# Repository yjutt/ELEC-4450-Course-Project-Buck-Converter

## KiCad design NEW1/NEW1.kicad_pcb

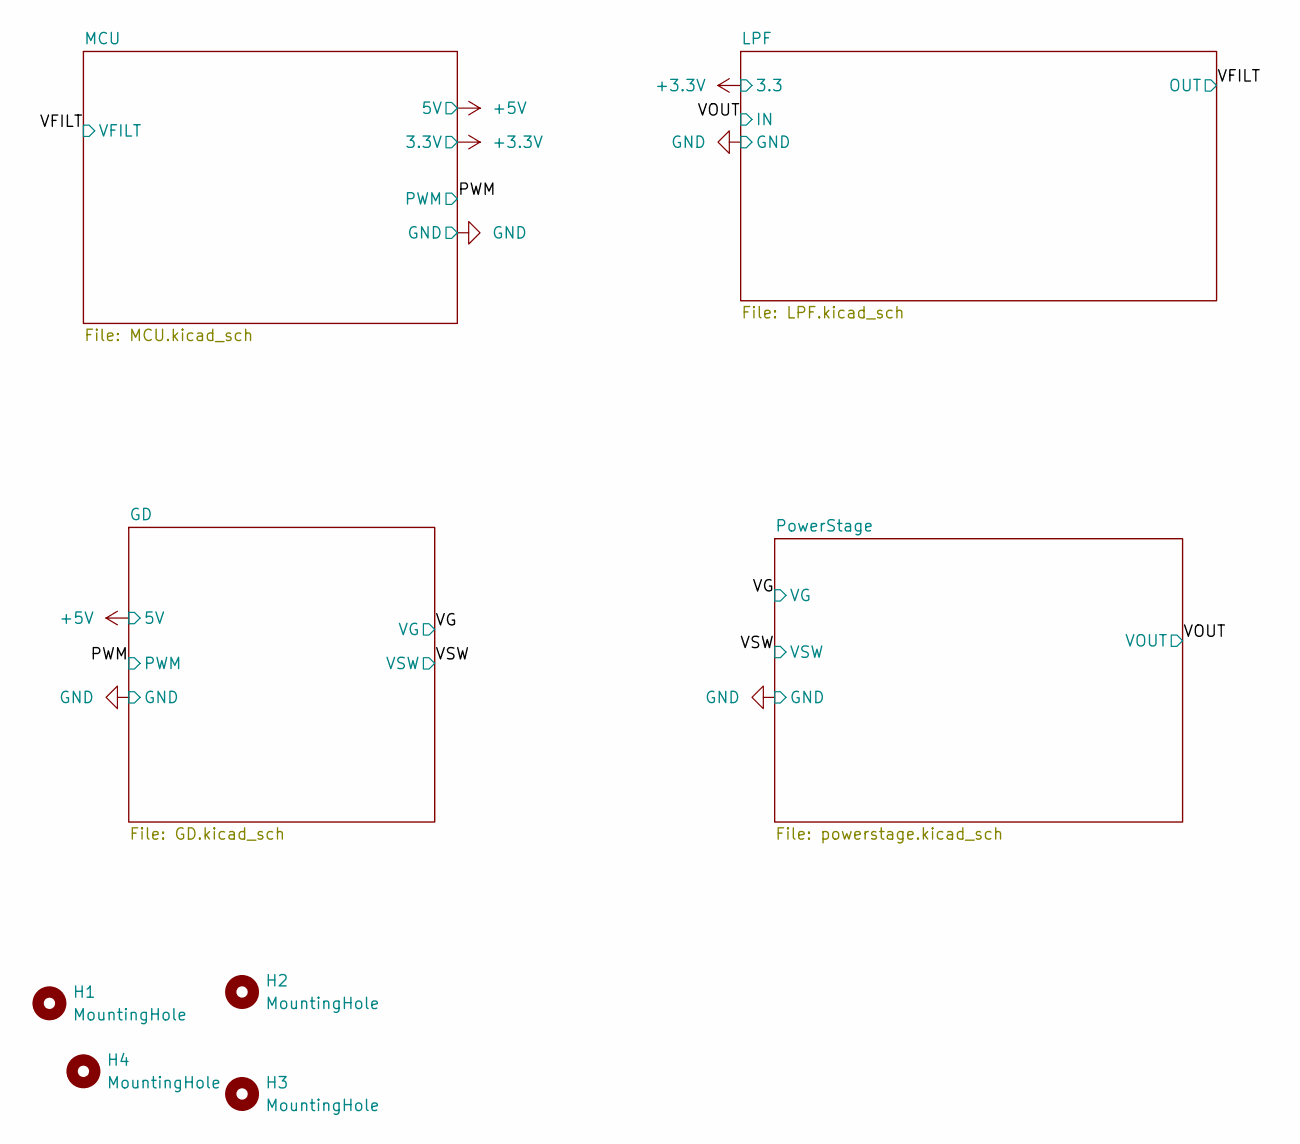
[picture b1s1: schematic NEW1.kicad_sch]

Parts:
H1, H2, H3, H4: MountingHole; MountingHole_4mm; Part Number 971100244

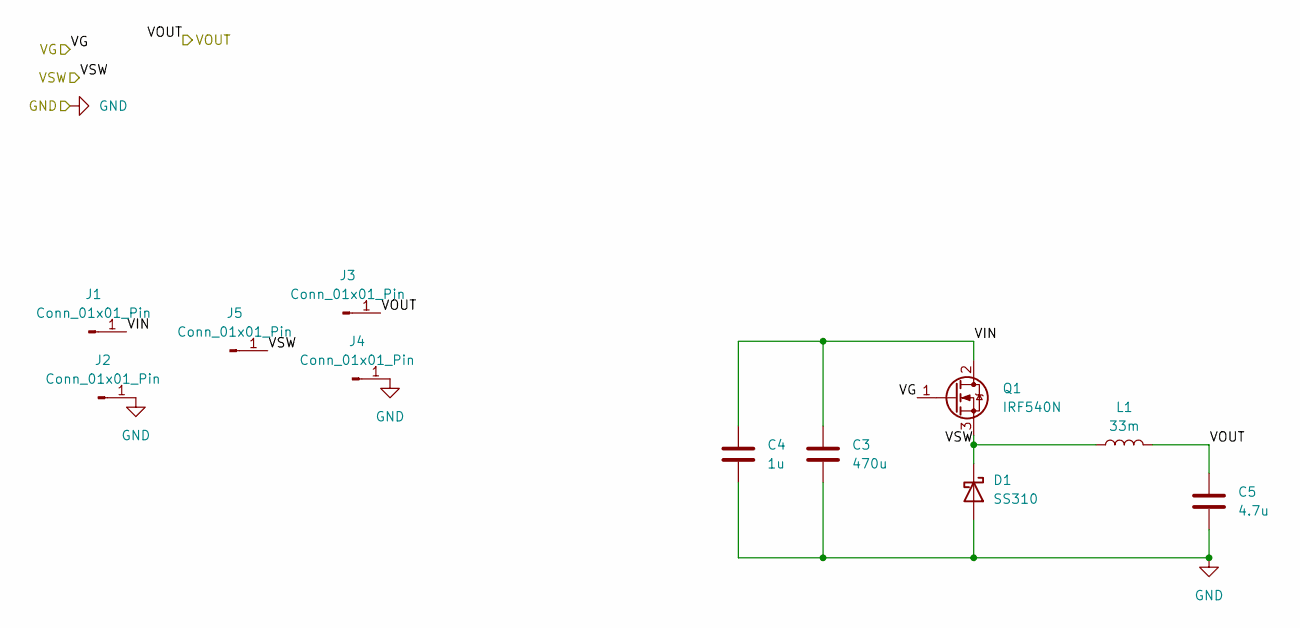
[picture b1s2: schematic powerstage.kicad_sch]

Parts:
C3: 470u; CP_Radial_D18.0mm_P7.50mm; Part Number 100ZLH470MEFC16X31.5
C4: 1u; C_0805_2012Metric; Part Number GRM21BC72A105KE01L
C5: 4.7u; C_1206_3216Metric; Part Number GRM31CC72A475KE11L
D1: SS310; D_SMA; Part Number SS310
J1, J2, J3, J4, J5: Conn_01x01_Pin; Banana_Jack_1Pin; Part Number BU-P72930-2
L1: 33m; L_Axial_L23.4mm_D12.7mm_P32.00mm_Horizontal_Vishay_IHA-203; Part Number 5900-333-RC
Q1: IRF540N; TO-220-3_Vertical; Part Number IRF540N

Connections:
/PowerStage/VIN: C3.1, C4.1, J1.1, Q1.2 (D)
/VG: Q1.1 (G); also elsewhere on the board
/VOUT: C5.1, J3.1, L1.2; also elsewhere on the board
/VSW: D1.1 (K), J5.1, L1.1, Q1.3 (S); also elsewhere on the board
GND: C3.2, C4.2, C5.2, D1.2 (A), J2.1, J4.1; also elsewhere on the board

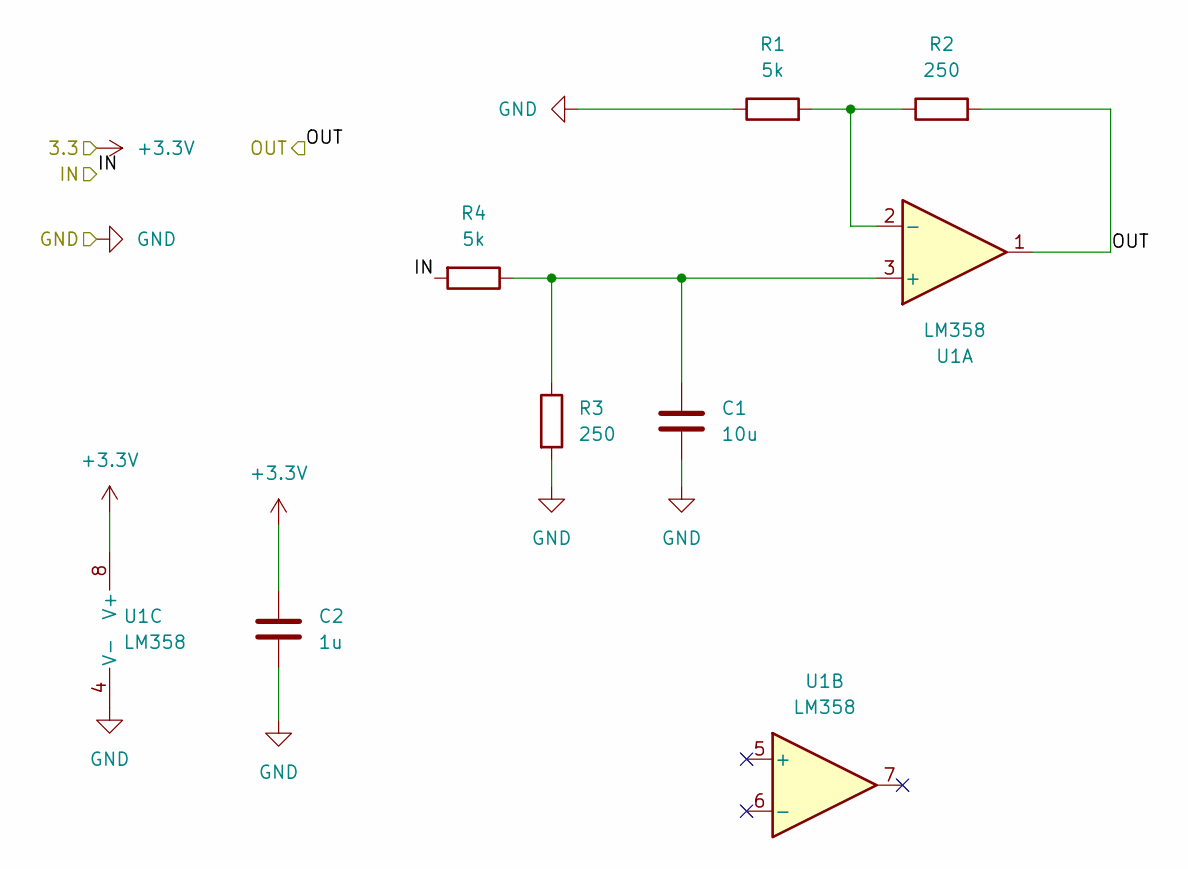
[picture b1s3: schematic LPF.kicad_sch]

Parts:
C1: 10u; C_0805_2012Metric; Part Number GRM21BR61C106KE15K
C2: 1u; C_0805_2012Metric; Part Number C0805C105K3RACTU
R1, R4: 5k; R_0805_2012Metric; Part Number CRT0805-BY-5001EAS
R2, R3: 250; R_0805_2012Metric; Part Number APC0805B250RN
U1: LM358; DIP-8_W7.62mm; Part Number LM358AP

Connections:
+3.3V: C2.1, U1.8 (V+); also elsewhere on the board
/VFILT: R2.2, U1.1; also elsewhere on the board
/VOUT: R4.2; also elsewhere on the board
GND: C1.2, C2.2, R1.1, R3.2, U1.4 (V-); also elsewhere on the board
unnamed: C1.1, R3.1, R4.1, U1.3 (+)
unnamed: R1.2, R2.1, U1.2 (-)

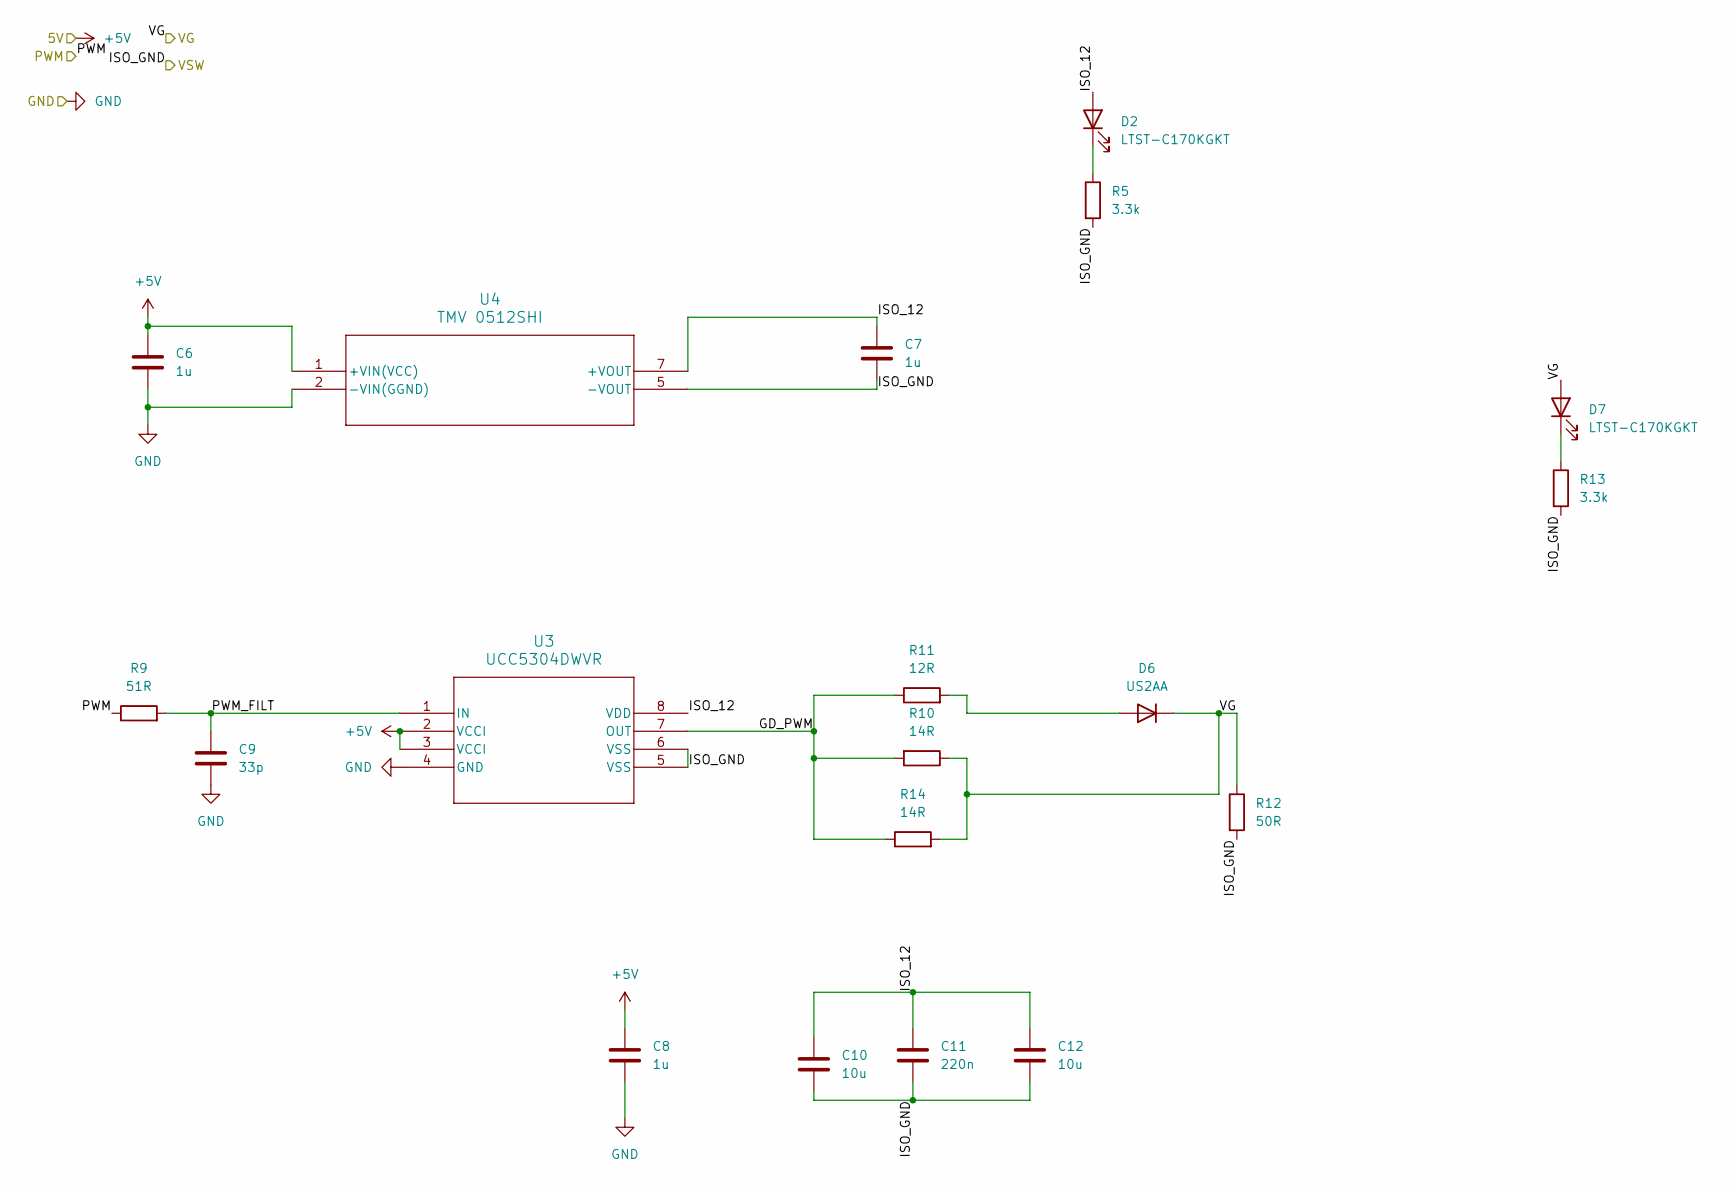
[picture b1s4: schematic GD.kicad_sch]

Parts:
C6, C7: 1u; C_0805_2012Metric; Part Number C0805C105K3RACTU
C8: 1u; C_0805_2012Metric_Pad1.18x1.45mm_HandSolder; Part Number C0805C105K3RACTU
C9: 33p; C_0805_2012Metric_Pad1.18x1.45mm_HandSolder; Part Number 600F330FT250XT4K
C10, C12: 10u; C_0805_2012Metric; Part Number F951C106MPAAQ2
C11: 220n; C_0805_2012Metric; Part Number C0805C224K5RACTU
D2, D7: LTST-C170KGKT; LED_0805_2012Metric; Part Number LTST-C170KGKT
D6: US2AA; D_SMA; Part Number US2AA
R5, R13: 3.3k; R_0805_2012Metric_Pad1.20x1.40mm_HandSolder; Part Number ERJ-P06F3301V
R9: 51R; R_0805_2012Metric_Pad1.20x1.40mm_HandSolder; Part Number RC0805FR-0751RL
R10, R14: 14R; R_0805_2012Metric_Pad1.20x1.40mm_HandSolder; Part Number RC0805FR-0714RL
R11: 12R; R_0805_2012Metric_Pad1.20x1.40mm_HandSolder; Part Number RC0805FR-0712RL
R12: 50R; R_1206_3216Metric_Pad1.30x1.75mm_HandSolder; Part Number RCP1206W50R0JTP
U3: UCC5304DWVR; SOIC8_DWV_TEX; Part Number UCC5304DWVR
U4: TMV 0512SHI; TMV-HI_SINGLE_TRP; Part Number TMV 0512SHI

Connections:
+5V: C6.1, C8.1, U3.2 (VCCI), U3.3 (VCCI), U4.1 (+VIN(VCC)); also elsewhere on the board
/GD/GD_PWM: R10.2, R11.1, R14.1, U3.7 (OUT)
/GD/ISO_12: C7.1, C10.1, C11.1, C12.1, D2.2 (A), U3.8 (VDD), U4.7 (+VOUT)
/GD/PWM_FILT: C9.1, R9.2, U3.1 (IN)
/PWM: R9.1; also elsewhere on the board
/VG: D6.1 (K), D7.2 (A), R10.1, R12.1, R14.2; also elsewhere on the board
/VSW: C7.2, C10.2, C11.2, C12.2, R5.2, R12.2, R13.2, U3.5 (VSS), U3.6 (VSS), U4.5 (-VOUT); also elsewhere on the board
GND: C6.2, C8.2, C9.2, U3.4 (GND), U4.2 (-VIN(GGND)); also elsewhere on the board
unnamed: D2.1 (K), R5.1
unnamed: D6.2 (A), R11.2
unnamed: D7.1 (K), R13.1

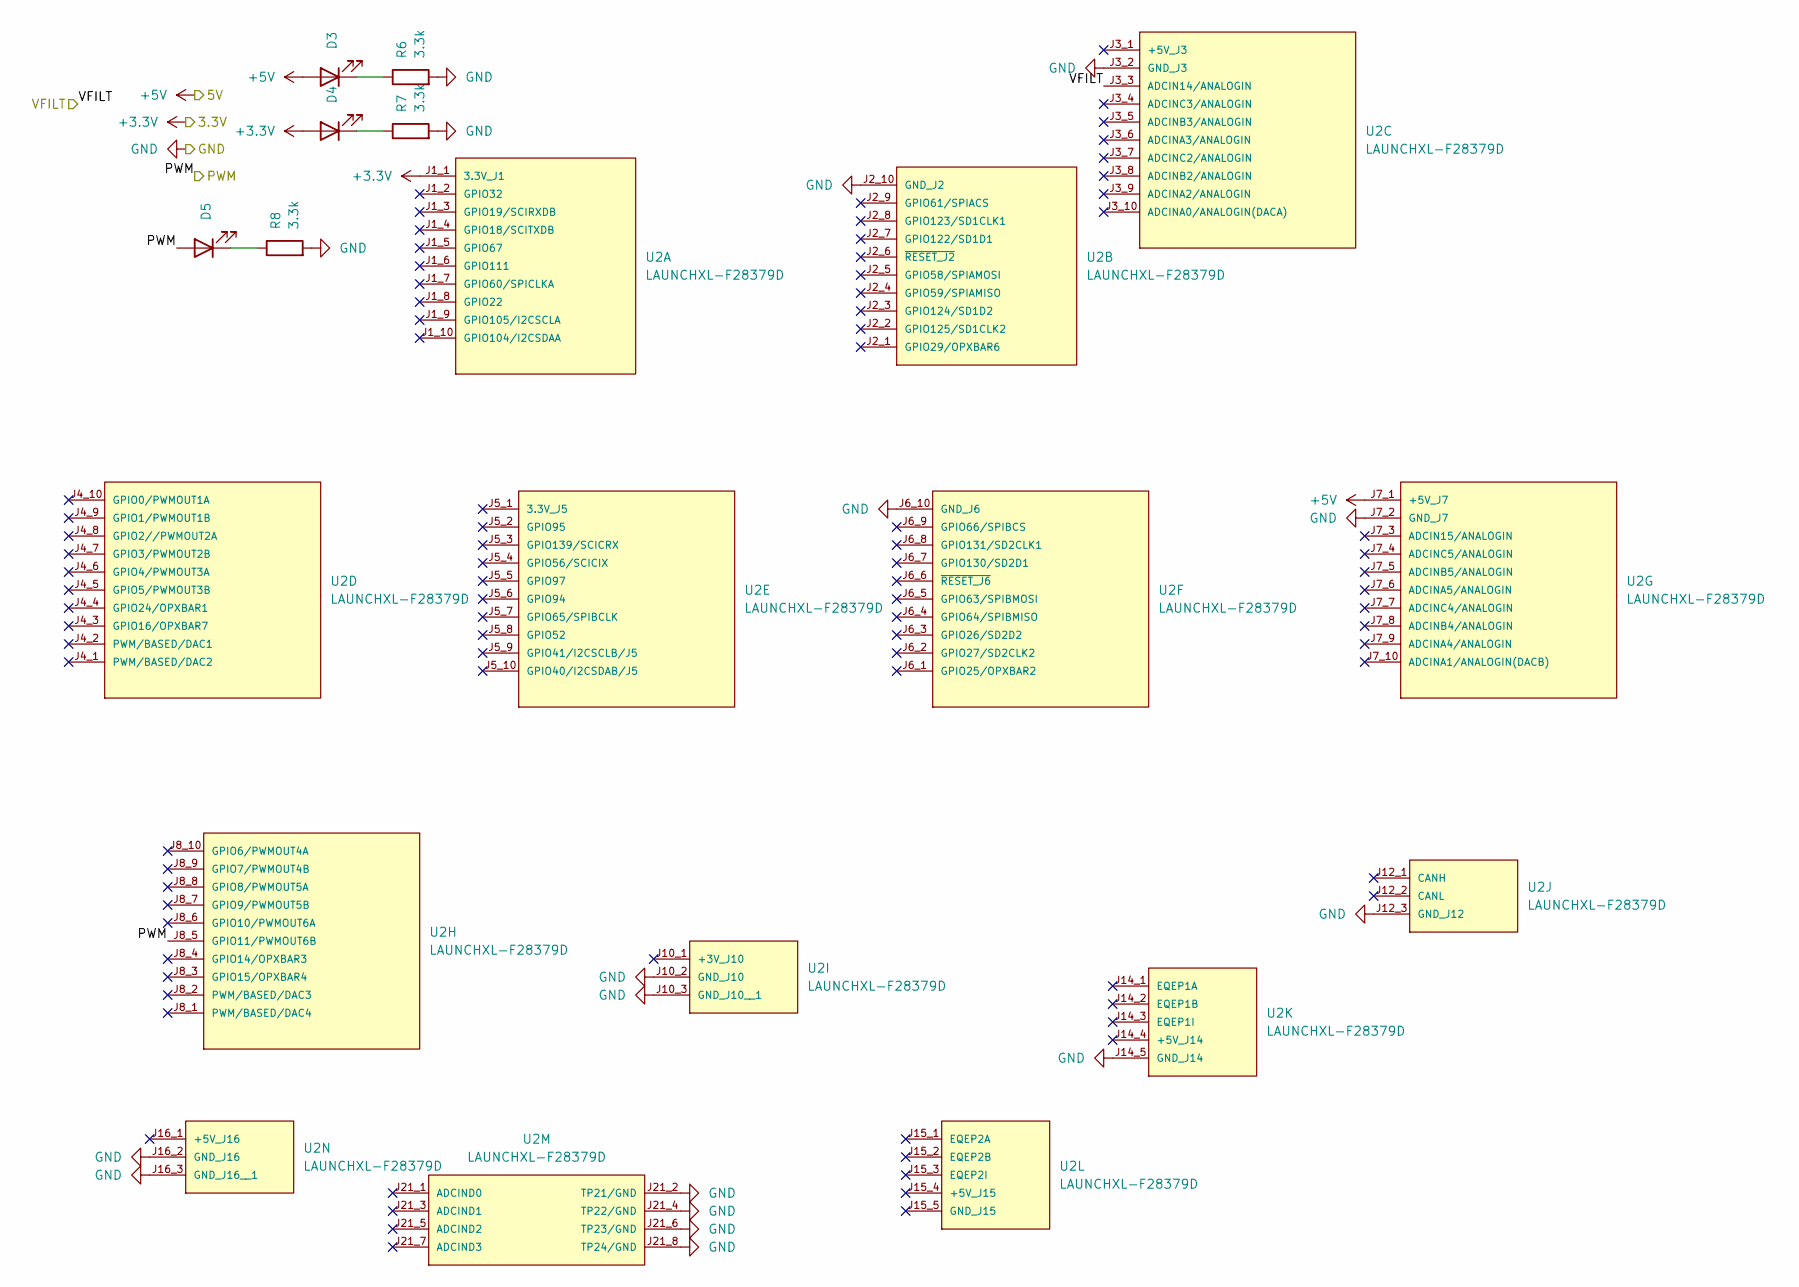
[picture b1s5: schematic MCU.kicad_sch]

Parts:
D3, D4, D5: LTST-C170KGKT; LED_0805_2012Metric; Part Number LTST-C170KGKT
R6, R7, R8: 3.3k; R_0805_2012Metric_Pad1.20x1.40mm_HandSolder; Part Number ERJ-P06F3301V
U2: LAUNCHXL-F28379D; MOD_LAUNCHXL-F28379D; PARTREV 2.0

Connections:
+3.3V: D4.2 (A), U2.J1_1 (3.3V_J1); also elsewhere on the board
+5V: D3.2 (A), U2.J7_1 (+5V_J7); also elsewhere on the board
/PWM: D5.2 (A), U2.J8_5 (GPIO11/PWMOUT6B); also elsewhere on the board
/VFILT: U2.J3_3 (ADCIN14/ANALOGIN); also elsewhere on the board
GND: R6.2, R7.2, R8.2, U2.J2_10 (GND_J2), U2.J3_2 (GND_J3), U2.J6_10 (GND_J6), U2.J7_2 (GND_J7), U2.J10_2 (GND_J10), U2.J10_3 (GND_J10__1), U2.J12_3 (GND_J12), U2.J14_5 (GND_J14), U2.J16_2 (GND_J16), U2.J16_3 (GND_J16__1), U2.J21_2 (TP21/GND), U2.J21_4 (TP22/GND), U2.J21_6 (TP23/GND), U2.J21_8 (TP24/GND); also elsewhere on the board
unnamed: D3.1 (K), R6.1
unnamed: D4.1 (K), R7.1
unnamed: D5.1 (K), R8.1

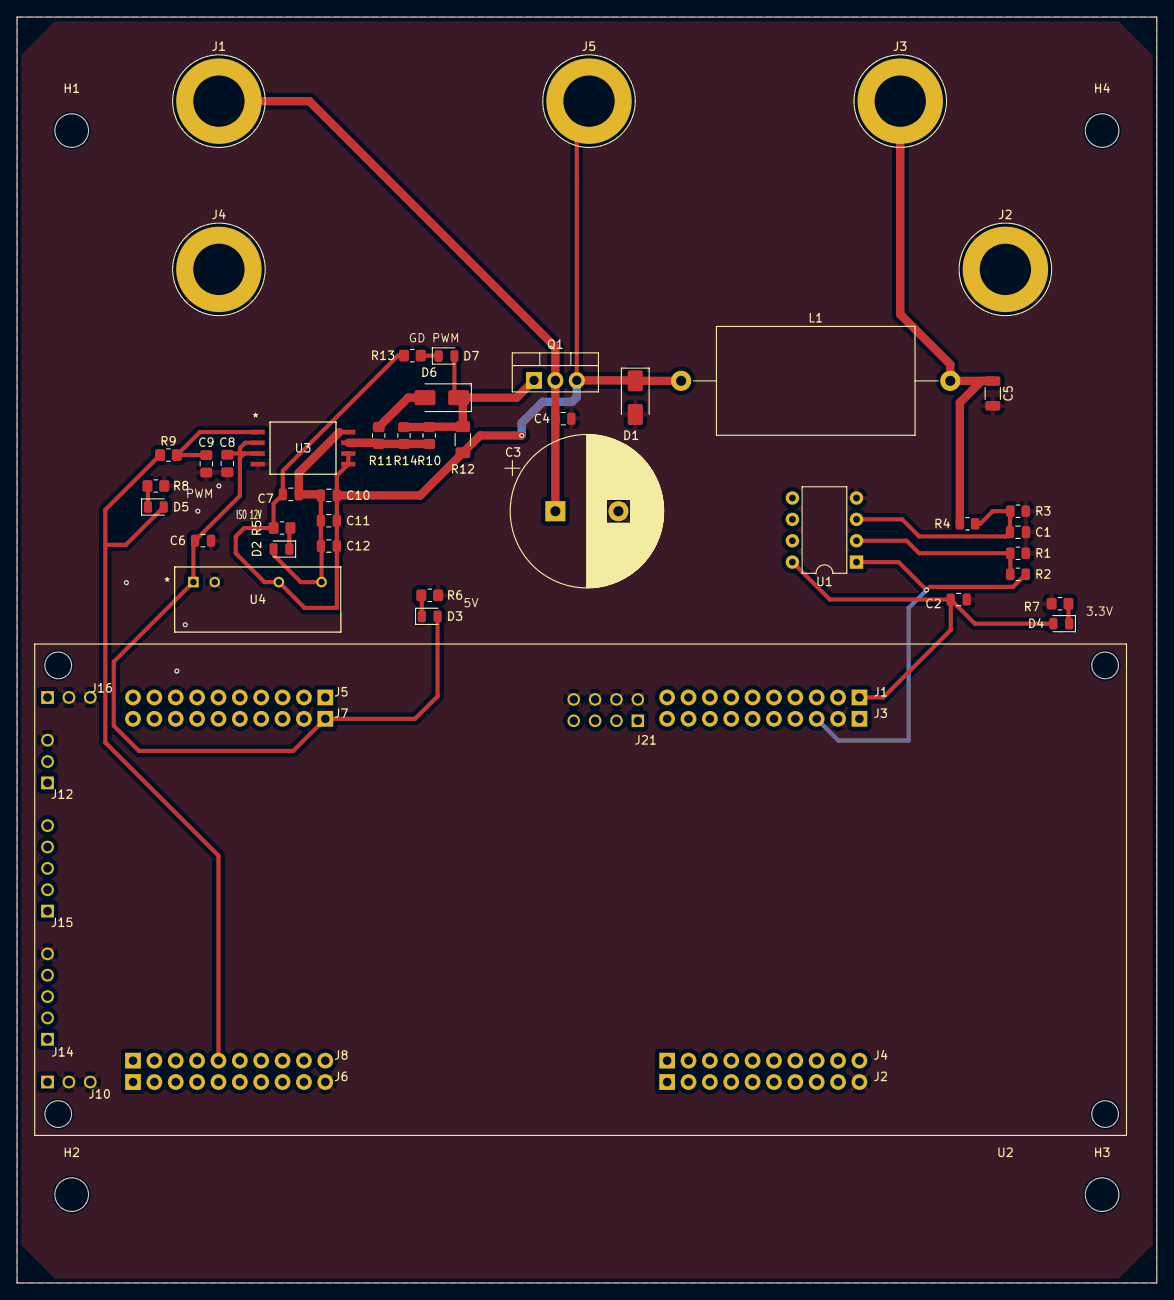
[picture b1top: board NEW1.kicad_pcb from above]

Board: 2 copper layers, 135.5 x 150.5 mm, 48 parts (0 on the bottom side), 20 nets.
